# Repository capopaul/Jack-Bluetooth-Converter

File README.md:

# Jack <> Bluetooth Converter

Revision 3.1 (Not manufactured yet) :

Revision 3.0 (Manufactured) :

## Table of Content

1. [Features](#1-features)
2. [Design Specificatin and documentation](#2-design-specification-and-documentation)
3. [Repo organization](#3-repo-organization)
4. [Next steps](#4-next-steps)
5. [Revision history](#5-revisions-history)

## 1. Features

This project aims to design a device with the following features:

- Audio input from a 2.5mm audio jack can be sampled and transmitted via Bluetooth to a headphone.
- Digital audio from a smartphone can be received via Bluetooth and converted into analog audio through a 3.5mm audio jack.
- The device can be powered via USB-C or run on battery for up to 3 hours.
- The battery charges when the device is connected to USB-C.
- A screen and buttons allow switching between "Jack to Bluetooth" and "Bluetooth to Jack" modes.
- The screen and buttons enable Bluetooth peripheral selection when the device functions as a Bluetooth central.
- The screen turns off after 1 minute of inactivity to save power.

## 2. Design specification and documentation

Please go to [Jack <> Bluetooth Design Specification](doc/Jack<>Bluetooth-Design-Specification.md) which documents the design choices and provide details on the project.

[Software Readme](software/README.md) contains note taking from the software development (work in progress).

## 3. Repo organization

`./Components` -> components list with libs (not public)

`./doc` -> documentations, specifications and images

`./gerber` -> pcb design files for manufacturing

`./kicad` -> Kicad files

`./software` -> ESP32 C code (work in progress)

## 4. Next steps

- Working on a new revision : Rev3.1 to fix the current hardware limitations

## 5. Revisions history

Please go to [Jack<>Bluetooth-Revision-History](doc/Jack<>Bluetooth-Revision-History.md)

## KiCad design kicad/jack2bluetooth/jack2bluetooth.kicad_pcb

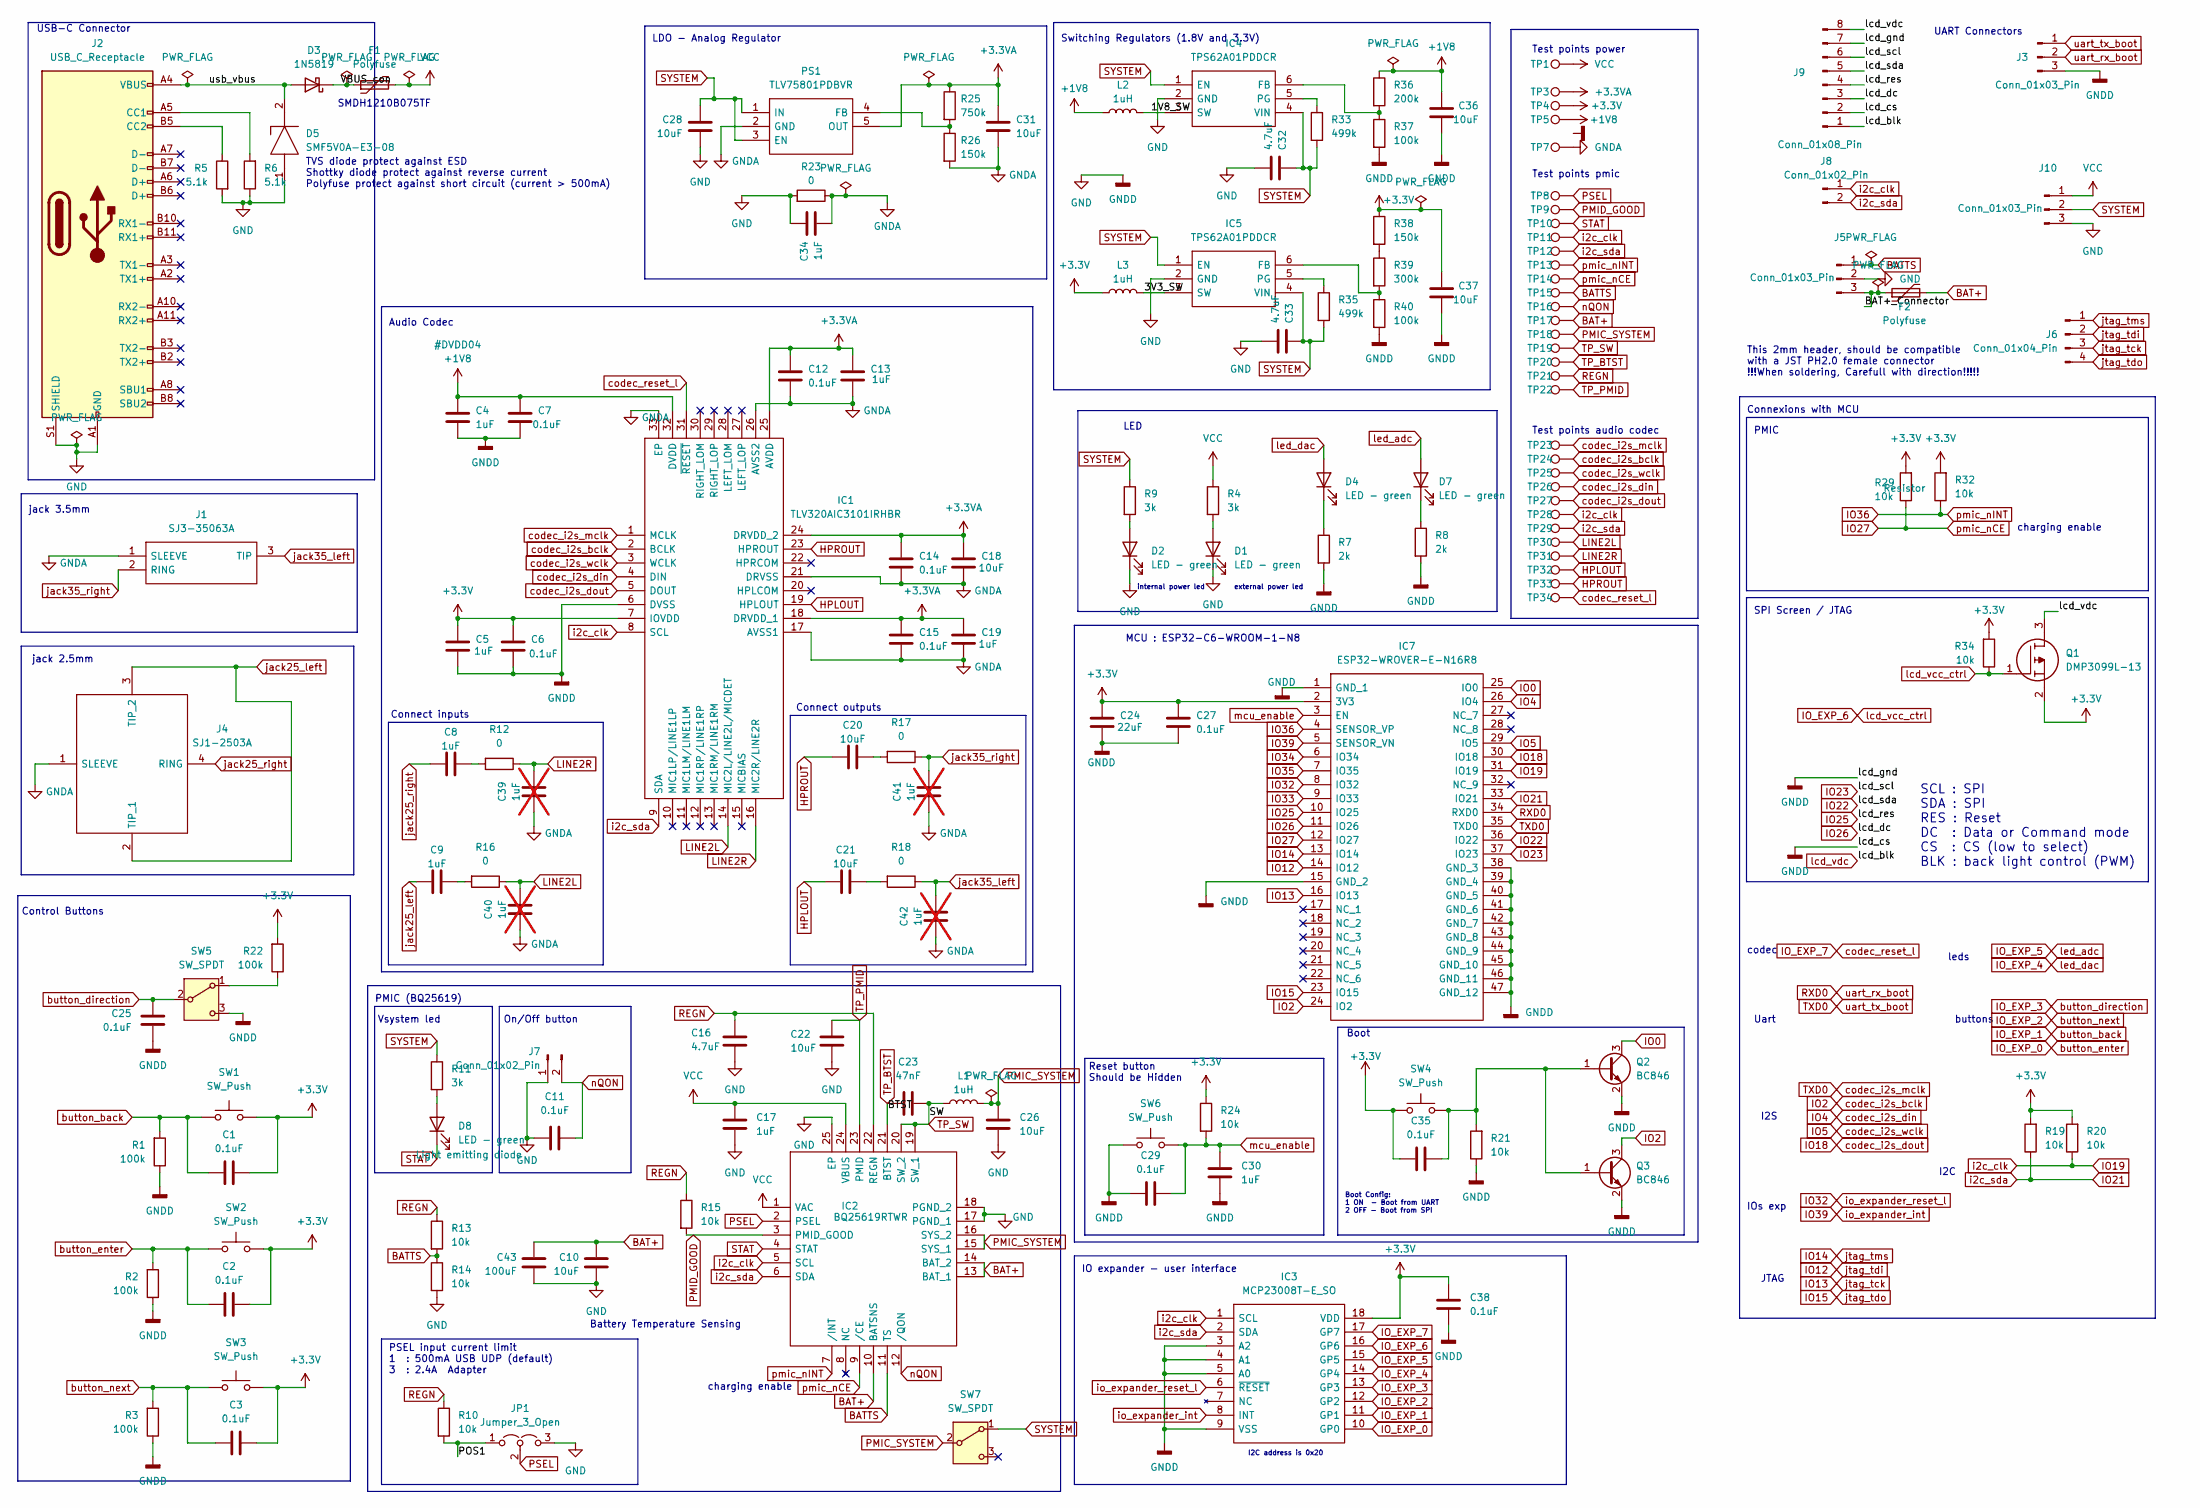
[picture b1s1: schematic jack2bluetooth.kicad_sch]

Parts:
C1, C2, C3, C6, C7, C11, C12, C14, C15, C25, C27, C29, C35, C38: 0.1uF; C_0805_2012Metric_Pad1.18x1.45mm_HandSolder
C4, C5, C8, C9, C13, C17, C19, C30, C34: 1uF; C_0805_2012Metric_Pad1.18x1.45mm_HandSolder
C10, C18, C20, C21, C22, C26, C28, C31, C36, C37: 10uF; C_0805_2012Metric_Pad1.18x1.45mm_HandSolder
C16, C32, C33: 4.7uF; C_0805_2012Metric_Pad1.18x1.45mm_HandSolder
C23: 47nF; C_0805_2012Metric_Pad1.18x1.45mm_HandSolder
C24: 22uF; C_0805_2012Metric_Pad1.18x1.45mm_HandSolder
C39, C40, C41, C42: 1uF; C_0805_2012Metric_Pad1.18x1.45mm_HandSolder; not fitted
C43: 100uF; C_0805_2012Metric_Pad1.18x1.45mm_HandSolder
D1, D2, D4, D7, D8: LED - green; LED_0805_2012Metric_Pad1.15x1.40mm_HandSolder
D3: 1N5819; D_SOD-123
D5: SMF5V0A-E3-08; SMF5V0AE308; Mouser Part Number 78-SMF5V0A-E3-08
F1, F2: Polyfuse; Fuse_1210_3225Metric_Pad1.42x2.65mm_HandSolder
IC1: TLV320AIC3101IRHBR; QFN50P500X500X100-33N-D; Mouser Part Number 595-T320AIC3101IRHBR
IC2: BQ25619RTWR; QFN50P400X400X80-25N-D; Mouser Part Number 595-BQ25619RTWR
IC3: MCP23008T-E_SO; SOIC127P1030X265-18N; Mouser Part Number 579-MCP23008T-E/SO
IC4, IC5: TPS62A01PDDCR; SOT95P280X110-6N; Manufacturer_Part_Number TPS62A01PDDCR
IC7: ESP32-WROVER-E-N16R8; ESP32WROVEREN16R8; Mouser Part Number 356-ESP32WRVE22864PC
J1: SJ3-35063A; SJ335063A; Mouser Part Number 179-SJ3-35063A
J2: USB_C_Receptacle; USB_C_Receptacle_GCT_USB4105-xx-A_16P_TopMnt_Horizontal
J3, J5, J10: Conn_01x03_Pin; PinHeader_1x03_P2.54mm_Vertical
J4: SJ1-2503A; SJ12503A; Mouser Part Number 490-SJ1-2503A
J6: Conn_01x04_Pin; PinHeader_1x04_P2.54mm_Vertical
J7: Conn_01x02_Pin; PinHeader_1x02_P2.54mm_Vertical
J8: Conn_01x02_Pin; PinHeader_1x02_P2.00mm_Vertical
J9: Conn_01x08_Pin; PinHeader_1x08_P2.54mm_Vertical
JP1: Jumper_3_Open; PinHeader_1x03_P2.54mm_Vertical
L1: 1uH; L_0805_2012Metric_Pad1.05x1.20mm_HandSolder
L2, L3: 1uH; L_0805_2012Metric
PS1: TLV75801PDBVR; SOT95P280X145-5N; Mouser Part Number 595-TLV75801PDBVR
Q1: DMP3099L-13; SOT96P240X115-3N; Mouser Part Number 621-DMP3099L-13
Q2, Q3: BC846; SOT-23
R1, R2, R3, R22, R37, R40: 100k; R_0805_2012Metric_Pad1.20x1.40mm_HandSolder
R4, R9, R11: 3k; R_0805_2012Metric_Pad1.20x1.40mm_HandSolder
R5, R6: 5.1k; R_0805_2012Metric_Pad1.20x1.40mm_HandSolder
R7, R8: 2k; R_0805_2012Metric_Pad1.20x1.40mm_HandSolder
R10, R13, R14, R15, R19, R20, R21, R24, R29, R32, R34: 10k; R_0805_2012Metric_Pad1.20x1.40mm_HandSolder
R12, R16, R17, R18, R23: 0; R_0805_2012Metric_Pad1.20x1.40mm_HandSolder
R25: 750k; R_0805_2012Metric_Pad1.20x1.40mm_HandSolder
R26, R38: 150k; R_0805_2012Metric_Pad1.20x1.40mm_HandSolder
R33, R35: 499k; R_0805_2012Metric_Pad1.20x1.40mm_HandSolder
R36: 200k; R_0805_2012Metric_Pad1.20x1.40mm_HandSolder
R39: 300k; R_0805_2012Metric_Pad1.20x1.40mm_HandSolder
SW1, SW2, SW3, SW4, SW6: SW_Push; SW_PUSH_6mm
SW5, SW7: SW_SPDT; SLW-105558-2A-N-D
TP1, TP3, TP4, TP5, TP7, TP8, TP9, TP10, TP11, TP12, TP13, TP14, TP15, TP16, TP17, TP18, TP19, TP20, TP21, TP22, TP23, TP24, TP25, TP26, TP27, TP28, TP29, TP30, TP31, TP32, TP33, TP34: TestPoint; TestPoint_Pad_D1.0mm

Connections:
+1V8: C4.1, C7.1, C36.1, IC1.32 (DVDD), L2.1, R36.1, TP5.1
+3.3V: C1.1, C2.1, C3.1, C5.1, C6.1, C24.1, C27.1, C35.2, C37.1, C38.1, IC1.7 (IOVDD), IC3.18 (VDD), IC7.2 (3V3), L3.1, Q1.2, R19.2, R20.2, R22.2, R24.1, R29.2, R32.2, R34.2, R38.1, SW1.2, SW2.2, SW3.2, SW4.1, TP4.1
+3.3VA: C12.1, C13.1, C14.1, C15.1, C18.1, C19.1, C31.1, IC1.18 (DRVDD_1), IC1.24 (DRVDD_2), IC1.25 (AVDD), PS1.5 (OUT), R25.1, TP3.1
/1V8_SW: IC4.3 (SW), L2.2
/3V3_SW: IC5.3 (SW), L3.2
/BAT+_Connector: F2.1, J5.3
/POS1: JP1.1 (A), R10.2
/VBUS_con: D3.1 (K), F1.1
/usb_vbus: D3.2 (A), D5.2, J2.A4 (VBUS), J2.A9 (VBUS), J2.B4 (VBUS), J2.B9 (VBUS)
BAT+: C10.1, C43.1, F2.2, IC2.10 (BATSNS), IC2.13 (BAT_1), IC2.14 (BAT_2), TP17.1
BATTS: IC2.11 (TS), J5.1, R13.2, R14.1, TP15.1
GND: C4.2, C5.2, C6.2, C7.2, C10.2, C11.2, C16.1, C17.2, C22.1, C24.2, C25.2, C26.1, C27.2, C28.2, C29.2, C30.2, C32.2, C33.2, C34.1, C36.2, C37.2, C38.2, C43.2, D1.1 (K), D2.1 (K), D5.1, IC1.6 (DVSS), IC2.17 (PGND_1), IC2.18 (PGND_2), IC2.25 (EP), IC3.3 (A2), IC3.4 (A1), IC3.5 (A0), IC3.9 (VSS), IC4.2 (GND), IC5.2 (GND), IC7.1 (GND_1), IC7.15 (GND_2), IC7.38 (GND_3), IC7.39 (GND_4), IC7.40 (GND_5), IC7.41 (GND_6), IC7.42 (GND_7), IC7.43 (GND_8), IC7.44 (GND_9), IC7.45 (GND_10), IC7.46 (GND_11), IC7.47 (GND_12), J2.A1 (GND), J2.A12 (GND), J2.B1 (GND), J2.B12 (GND), J2.S1 (SHIELD), J3.3, J5.2, J7.1, J9.2, J9.7, J10.3, JP1.3 (B), Q2.2 (E), Q3.2 (E), R1.1, R2.1, R3.1, R5.2, R6.1, R7.2, R8.2, R14.2, R21.1, R23.2, R37.2, R40.2, SW5.3 (C), SW6.1
GNDA: C12.2, C13.2, C14.2, C15.2, C18.2, C19.2, C31.2, C34.2, C39.1, C40.1, C41.1, C42.1, IC1.17 (AVSS1), IC1.21 (DRVSS), IC1.26 (AVSS2), IC1.33 (EP), J1.1 (SLEEVE), J4.1 (SLEEVE), PS1.2 (GND), R23.1, R26.2, TP7.1
HPLOUT: C21.1, IC1.19 (HPLOUT), TP32.1
HPROUT: C20.1, IC1.23 (HPROUT), TP33.1
IO0: IC7.25 (IO0), Q2.3 (C)
IO2: IC1.2 (BCLK), IC7.24 (IO2), Q3.3 (C), TP24.1
IO4: IC1.4 (DIN), IC7.26 (IO4), TP26.1
IO5: IC1.3 (WCLK), IC7.29 (IO5), TP25.1
IO12: IC7.14 (IO12), J6.2
IO13: IC7.16 (IO13), J6.3
IO14: IC7.13 (IO14), J6.1
IO15: IC7.23 (IO15), J6.4
IO18: IC1.5 (DOUT), IC7.30 (IO18), TP27.1
IO19: IC1.8 (SCL), IC2.5 (SCL), IC3.1 (SCL), IC7.31 (IO19), J8.1, R20.1, TP11.1, TP28.1
IO21: IC1.9 (SDA), IC2.6 (SDA), IC3.2 (SDA), IC7.33 (IO21), J8.2, R19.1, TP12.1, TP29.1
IO22: IC7.36 (IO22), J9.5
IO23: IC7.37 (IO23), J9.6
IO25: IC7.10 (IO25), J9.4
IO26: IC7.11 (IO26), J9.3
IO27: IC2.9 (/CE), IC7.12 (IO27), R29.1, TP14.1
IO32: IC3.6 (~RESET), IC7.8 (IO32)
IO33: IC7.9 (IO33)
IO34: IC7.6 (IO34)
IO35: IC7.7 (IO35)
IO36: IC2.7 (/INT), IC7.4 (SENSOR_VP), R32.1, TP13.1
IO39: IC3.8 (INT), IC7.5 (SENSOR_VN)
IO_EXP_0: C2.2, IC3.10 (GP0), R2.2, SW2.1
IO_EXP_1: C1.2, IC3.11 (GP1), R1.2, SW1.1
IO_EXP_2: C3.2, IC3.12 (GP2), R3.2, SW3.1
IO_EXP_3: C25.1, IC3.13 (GP3), SW5.2 (B)
IO_EXP_4: D4.2 (A), IC3.14 (GP4)
IO_EXP_5: D7.2 (A), IC3.15 (GP5)
IO_EXP_6: IC3.16 (GP6), Q1.1, R34.1
IO_EXP_7: IC1.31 (~RESET), IC3.17 (GP7), TP34.1
LINE2L: C40.2, IC1.14 (MIC2L/LINE2L/MICDET), R16.1, TP30.1
LINE2R: C39.2, IC1.16 (MIC2R/LINE2R), R12.1, TP31.1
unnamed: C8.2, R12.2
unnamed: C9.2, R16.2
unnamed: C20.2, R17.2
unnamed: C21.2, R18.2
unnamed: D1.2 (A), R4.2
unnamed: D2.2 (A), R9.2
unnamed: D4.1 (K), R7.1
unnamed: D7.1 (K), R8.1
unnamed: D8.2 (A), R11.2
unnamed: IC4.6 (FB), R36.2, R37.1
unnamed: IC4.5 (PG), R33.1
unnamed: IC5.6 (FB), R39.2, R40.1
unnamed: IC5.5 (PG), R35.1
unnamed: J2.A5 (CC1), R6.2
unnamed: J2.B5 (CC2), R5.1
unnamed: PS1.4 (FB), R25.2, R26.1
unnamed: C35.1, Q2.1 (B), Q3.1 (B), R21.2, SW4.2
unnamed: R38.2, R39.1
unnamed: R22.1, SW5.1 (A)
PMIC_SYSTEM: C26.2, IC2.15 (SYS_1), IC2.16 (SYS_2), L1.2, SW7.2 (B), TP18.1
PMID_GOOD: IC2.3 (PMID_GOOD), R15.2, TP9.1
PSEL: IC2.2 (PSEL), JP1.2 (C), TP8.1
REGN: C16.2, IC2.22 (REGN), R10.1, R13.1, R15.1, TP21.1
RXD0: IC7.34 (RXD0), J3.2
STAT: D8.1 (K), IC2.4 (STAT), TP10.1
SYSTEM: C28.1, C32.1, C33.1, IC4.1 (EN), IC4.4 (VIN), IC5.1 (EN), IC5.4 (VIN), J10.2, PS1.1 (IN), PS1.3 (EN), R9.1, R11.1, R33.2, R35.2, SW7.1 (A)
TP_BTST: C23.1, IC2.21 (BTST), TP20.1
TP_PMID: C22.2, IC2.23 (PMID), TP22.1
TP_SW: C23.2, IC2.19 (SW_1), IC2.20 (SW_2), L1.1, TP19.1
TXD0: IC1.1 (MCLK), IC7.35 (TXD0), J3.1, TP23.1
VCC: C17.1, F1.2, IC2.1 (VAC), IC2.24 (VBUS), J10.1, R4.1, TP1.1
jack25_left: C9.1, J4.2 (TIP_1), J4.3 (TIP_2)
jack25_right: C8.1, J4.4 (RING)
jack35_left: C42.2, J1.3 (TIP), R18.1
jack35_right: C41.2, J1.2 (RING), R17.1
lcd_vdc: J9.1, J9.8, Q1.3
mcu_enable: C29.1, C30.1, IC7.3 (EN), R24.2, SW6.2
nQON: C11.1, IC2.12 (/QON), J7.2, TP16.1

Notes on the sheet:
jack 2.5mm
TVS diode protect against ESD Shottky diode protect against reverse current Polyfuse protect against short circuit (current > 500mA)
external power led
Battery Temperature Sensing
codec
charging enable
SCL : SPI SDA : SPI RES : Reset DC : Data or Command mode CS : CS (low to select) BLK : back light control (PWM)
Test points audio codec
IO expander - user interface
Switching Regulators (1.8V and 3.3V)
MCU : ESP32-C6-WROOM-1-N8
Boot Config: 1 ON - Boot from UART 2 OFF - Boot from SPI
On/Off button
jack 3.5mm
This 2mm header, should be compatible with a JST PH2.0 female connector !!!When soldering, Carefull with direction!!!!!
Control Buttons
UART Connectors
Reset button Should be Hidden
Test points pmic
buttons
Test points power
Audio Codec
I2C address is 0x20
internal power led
Connect outputs
I2C
PMIC (BQ25619)
Connexions with MCU
USB-C Connector
SPI Screen / JTAG
I2S
JTAG
PMIC
PSEL input current limit 1 : 500mA USB UDP (default) 3 : 2.4A Adapter
Boot
LDO - Analog Regulator
Uart
SMDH1210B075TF
Connect inputs
IOs exp

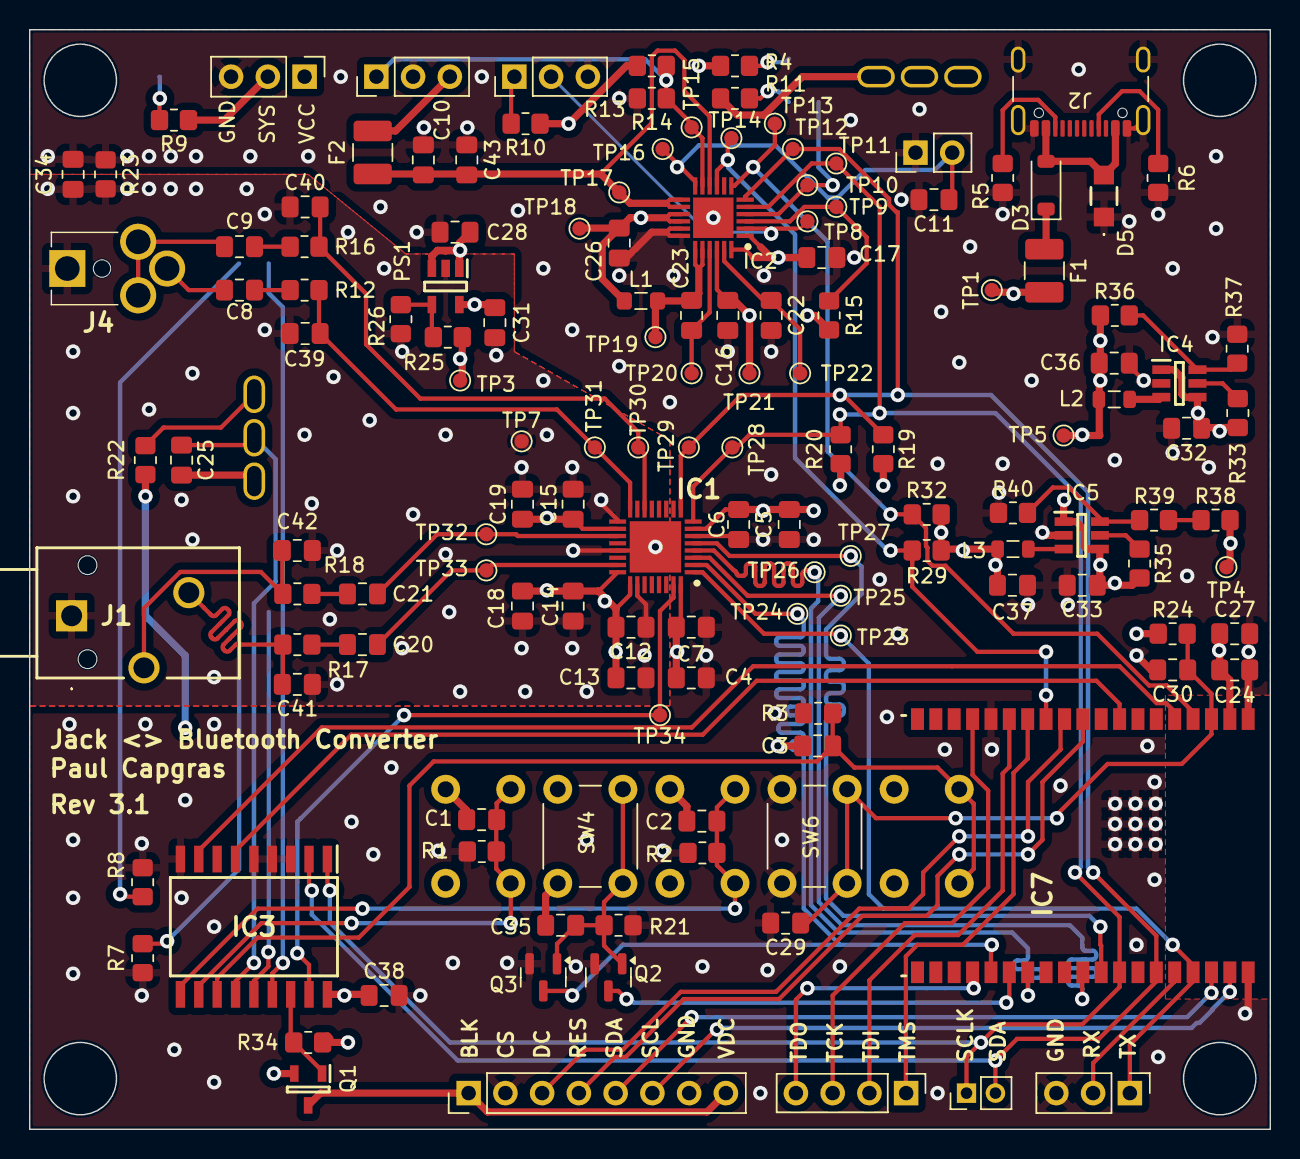
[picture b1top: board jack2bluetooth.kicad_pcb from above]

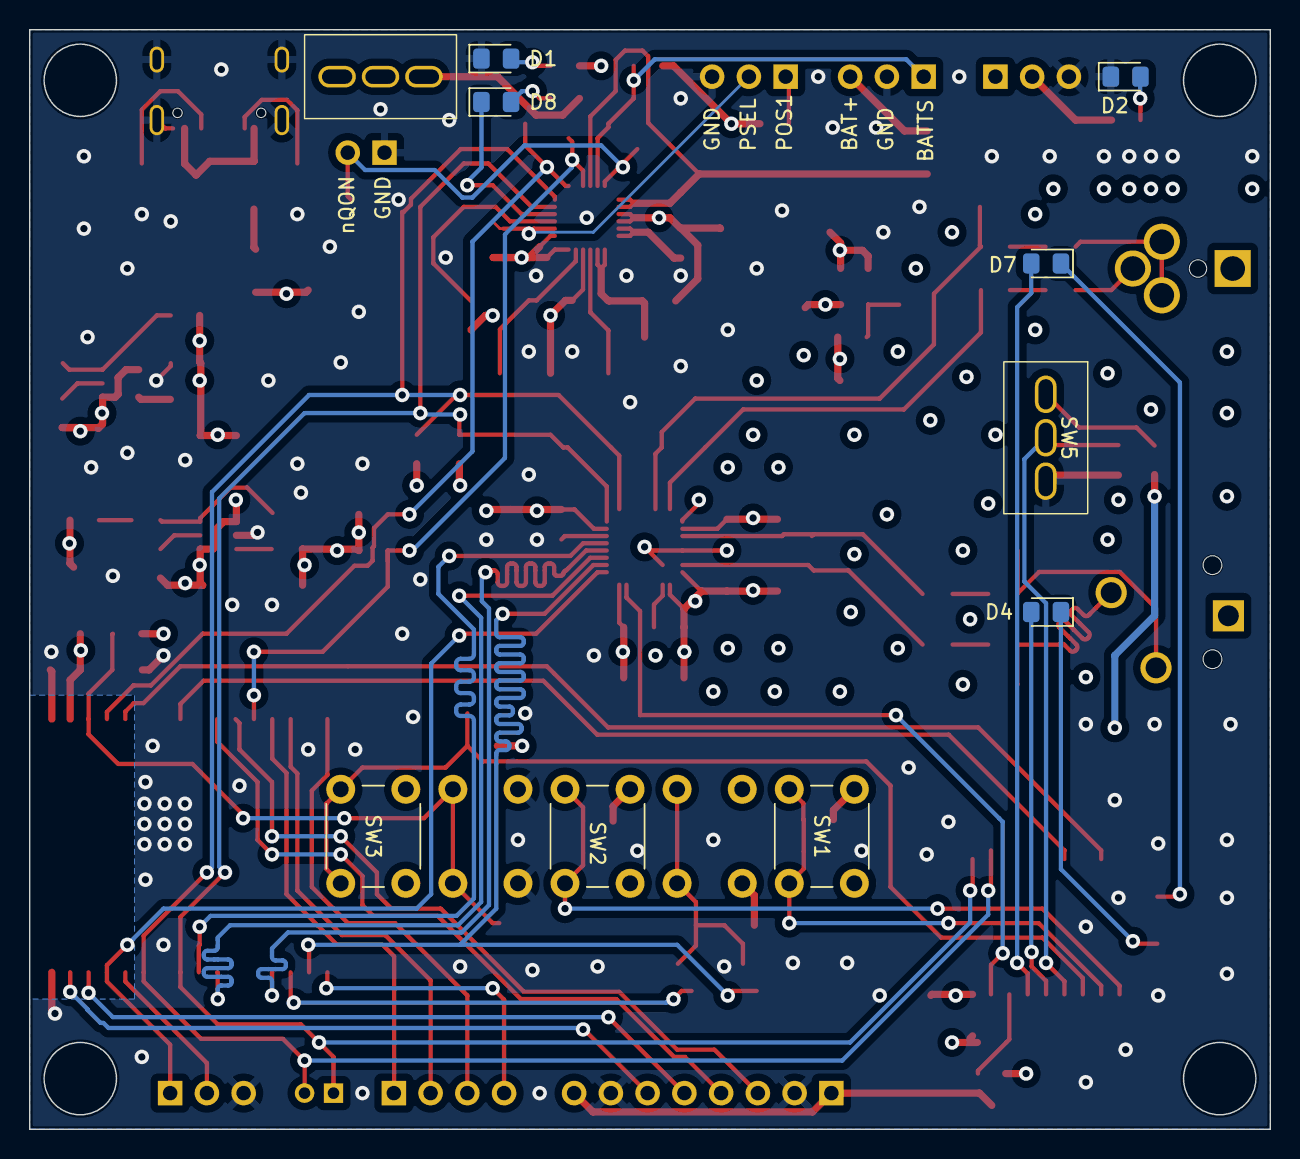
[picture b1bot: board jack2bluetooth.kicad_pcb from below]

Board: 4 copper layers, 85.8 x 76.0 mm, 151 parts (10 on the bottom side), 82 nets.

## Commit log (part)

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2025-02-24 doc: add design specification and gerber files
2025-02-24 doc: improve documentation, add readme sections
2025-02-24 doc: fix table of content title
2025-02-24 doc: improve documentation, add history and reorganize doc folder
2025-02-24 doc: wording
2025-11-10 feat: perform audio codec reset
2025-11-10 feat/doc june change
2025-11-10 doc: sept 17th work
2025-11-10 feat: copy a2dp sink example
2025-11-10 refactor: move everything in esp32_c6 folder
2025-11-10 feat: setup classic bt audio_sink on the esp32 using internal DAC.
2025-11-10 chore: fix path issues
2025-11-10 feat/doc : create esp32_i2c folder and update doc with the history of last work
2025-11-10 refactor: remove esp32c6 folder as I have removed the esp32 from the board
2025-11-10 doc: add board and new pinout
2025-11-10 feat: create esp32_b2j platform
2025-11-10 feat: configure audio-codec, clean i2c drivers and add doc to audio codec programming
2025-11-10 feat: add bluetooth connexion
2025-11-10 feat: setup to use the PLL instead of the MCLK. Add i2s waveforms from the oscilloscope
2025-11-10 refactor: rename esp folder
2025-11-10 feat: first stable platform with audio codec reset and bluetooth stack file. Bluetooth app not started yet.
2025-11-10 feat: update audio codec PLL to have BCLK=5.6MHz. Fail because the oscilloscope still get 1.4MHz
2025-11-10 feat: use BCLK = 2.822MHz
2025-11-10 refactor: move files from SW repo into SW folder
2025-11-10 doc: add pictures of manufacturing
2025-11-15 chore: update gerber files
2025-11-15 chore: add order folder to .gitignore
2025-11-16 doc: update pictures form rev3.0
2025-11-16 doc: add limitiations to revision history
2025-11-16 feat: select new MCU
2025-11-16 feat: add kicad folder with esp32 lib
2025-11-16 doc: update datasheets
2025-11-16 doc: update spec audio codec
2025-11-16 feat: add lib diode
2025-11-16 feat: add lib dip-switch
2025-11-16 feat: add lib jack2.5mm
2025-11-16 feat: add ldo lib
2025-11-16 feat: add pmic lib
2025-11-16 feat: add pmos lib
2025-11-16 feat: add slide-switch lib
2025-11-16 feat: add voltage regulator lib
2025-11-16 doc: update repo organization section
2025-11-17 feat: add io expander lib
2025-11-17 feat: add datasheets for esp32
2025-11-17 feat: add MCP eval board user guide
2025-11-17 doc: update design spec with IOs expander and rev3.1 modifications
2025-11-17 refactor: remove unused lib (diode)
2025-11-17 feat: update kicad schematic with rev3.1 updates
2025-11-20 feat: add datasheet for npn
2025-11-20 feat: add esp32 lyrat audio dev board schematic
2025-11-20 feat: update kicad schematic with latest Rev3.1 updates
2025-11-20 doc: update design spec and export schematic rev3.1 in pdf
2025-11-22 feat: add test points to schematic
2025-11-22 feat: update MCP23008 lib
2025-11-22 feat: add SMF5V0A lib
2025-11-22 refactor: remove unused datasheet
2025-11-22 feat: remove warnings in ERC errors and warnings in schematic. refresh layout
2025-12-15 feat: finish layout placement
2025-12-15 feat: update placement and update pin assignments for easier routing
2025-12-15 feat: route power
2026-02-19 feat: routing done, silkscreen done
2026-02-19 feat: length tuning, custom footprints and update doc
2026-02-19 Doc: update history with rev 3.1
2026-03-17 feat: generate gerber and bom
